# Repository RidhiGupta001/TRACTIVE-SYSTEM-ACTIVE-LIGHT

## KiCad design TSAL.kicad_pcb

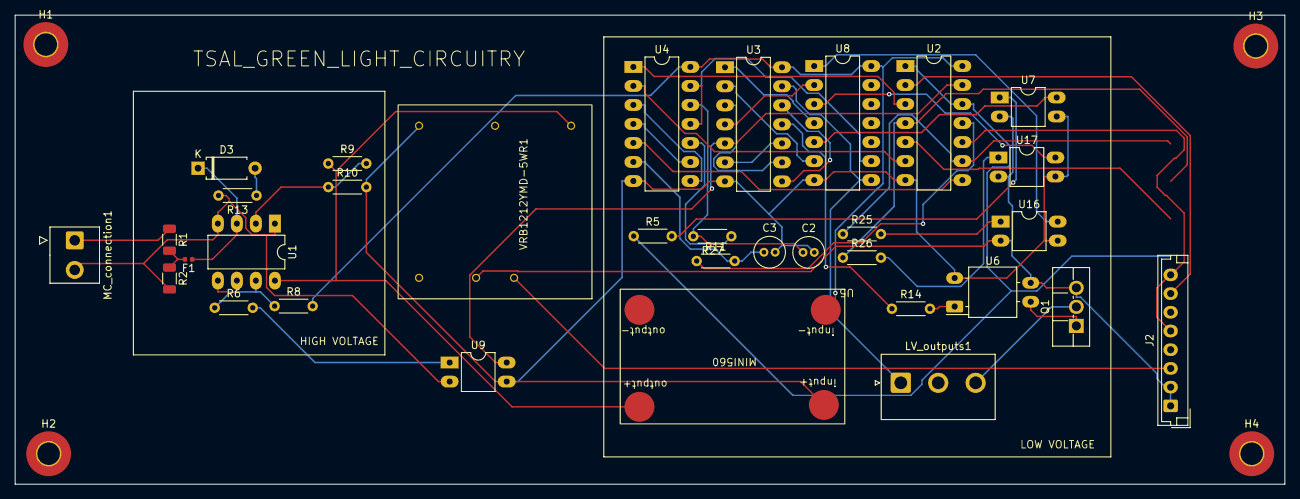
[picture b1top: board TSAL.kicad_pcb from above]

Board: 2 copper layers, 169.6 x 62.7 mm, 37 parts (0 on the bottom side), 48 nets.

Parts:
C2, C3: 47u; C_Radial_D4.0mm_H7.0mm_P1.50mm
D3: PTVS12VZ1USK; D_A-405_P7.62mm_Horizontal
F1: Fuse; Fuse_0402_1005Metric
H1, H2, H3, H4: MountingHole; MountingHole_3mm_Pad_TopBottom
J2: LV_INPUTS; JST_EH_B8B-EH-A_1x08_P2.50mm_Vertical
LV_outputs1: Conn_01x03; JST_NV_B03P-NV_1x03_P5.00mm_Vertical
MC_connection1: Conn_01x02; TE_826576-2_1x02_P3.96mm_Vertical
Q1: IRLIZ44N; TO-220F-3_Vertical
R1: 36M; R_1206_3216Metric
R2: 200k; R_1206_3216Metric
R5, R6, R13, R14, R25, R26: R_US; R_Axial_DIN0204_L3.6mm_D1.6mm_P5.08mm_Horizontal
R8: 10k; R_Axial_DIN0204_L3.6mm_D1.6mm_P5.08mm_Horizontal
R9: 36k; R_Axial_DIN0204_L3.6mm_D1.6mm_P5.08mm_Horizontal
R10: 1k; R_Axial_DIN0204_L3.6mm_D1.6mm_P5.08mm_Horizontal
R11: 180k; R_Axial_DIN0204_L3.6mm_D1.6mm_P5.08mm_Horizontal
R27: 5.1k; R_Axial_DIN0204_L3.6mm_D1.6mm_P5.08mm_Horizontal
U1: LM311; DIP-8_W7.62mm_LongPads
U2: 74HC86; DIP-14_W7.62mm_LongPads
U3: 74LS08; DIP-14_W7.62mm_LongPads
U4: 4071; DIP-14_W7.62mm_LongPads
U5: AMS1117-5.0; mini560
U6: NSL-32; Luna_NSL-32
U7, U9, U16, U17: NSL-32; DIP-4_W7.62mm_LongPads
U8: 74AHCT04; DIP-14_W7.62mm_LongPads
VRB1212YMD-5WR1: VRB1212YMD-5WR3

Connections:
5v: R8.2, U2.14 (VCC), U3.14 (VCC), U4.14 (VDD), U5.2 (VO), U8.14 (VCC)
12V_GLV: J2.2, VRB1212YMD-5WR1.2 (+Vin)
12v_isolated: R9.1, U1.8 (V+), U5.3 (VI), VRB1212YMD-5WR1.3 (+Vo)
AIR+: J2.5, R5.1, U2.1, U2.12
AIR-: J2.7, R26.1, U2.4
AUX_AIR +: J2.4, U2.2
AUX_AIR -: J2.6, U2.5
GNDREF: C2.2, C3.2, R10.2, U2.7 (GND), U3.7 (GND), U4.7 (VSS), U5.1 (GND), U6.2 (K), U7.3 (R), U8.7 (GND), U9.3 (R), U16.3 (R), U17.3 (R), VRB1212YMD-5WR1.5 (GND)
GREEN_LIGHT_OUT: LV_outputs1.3, Q1.2 (D)
Green_light_signal: R14.1, U3.11
LV_GND: J2.1, Q1.3 (S), U6.3 (R), U7.2 (K), U16.2 (K), U17.2 (K), VRB1212YMD-5WR1.1 (-Vin)
MC+: MC_connection1.1, R1.1
MC-: MC_connection1.2, R2.2, R13.2, U1.1 (GND), U1.4 (V-), U9.2 (K)
unnamed: C2.1, R27.2, U4.12
unnamed: C3.1, R11.2, U4.6
unnamed: D3.2 (A), R13.1
unnamed: D3.1 (K), F1.1, U1.3 (-)
unnamed: F1.2, R1.2, R2.1
unnamed: Q1.1 (G), U6.4 (R)
unnamed: R11.1, U2.11
unnamed: R27.1, U4.10
unnamed: R9.2, R10.1, U1.2 (+)
unnamed: U1.5 (BAL), U1.6 (STRB)
unnamed: U2.3, U4.1
unnamed: U2.6, U4.2
unnamed: U2.8, U4.5
unnamed: U3.3, U3.9
unnamed: U3.6, U3.10
unnamed: U3.8, U3.12
unnamed: U4.3, U4.8
unnamed: U4.4, U4.9
unnamed: U4.11, U4.13, U8.9
unnamed: R14.2, U6.1 (A)
unnamed: R5.2, U7.1 (A)
unnamed: U7.4 (R), U8.5
unnamed: R6.2, U9.1 (A)
unnamed: R25.2, U16.1 (A)
unnamed: R26.2, U17.1 (A)
unnamed: U8.3, U17.4 (R)
SAFE_STATE: U3.13, U8.8
\ 60v_flag: R6.1, R8.1, U1.7
\ precharge(TSMS): U3.4, U8.2
\AIR+: U3.2, U8.6
\AIR-: U3.1, U8.4
precharge(TSMS): U2.9, U8.1, U16.4 (R)
precharge(TSMS)_lv: J2.8, R25.1
precharge_NC: J2.3, U2.10
/60V_isolated: U2.13, U3.5, U9.4 (R)

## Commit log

2024-09-17 Add files via upload
    INITIAL
